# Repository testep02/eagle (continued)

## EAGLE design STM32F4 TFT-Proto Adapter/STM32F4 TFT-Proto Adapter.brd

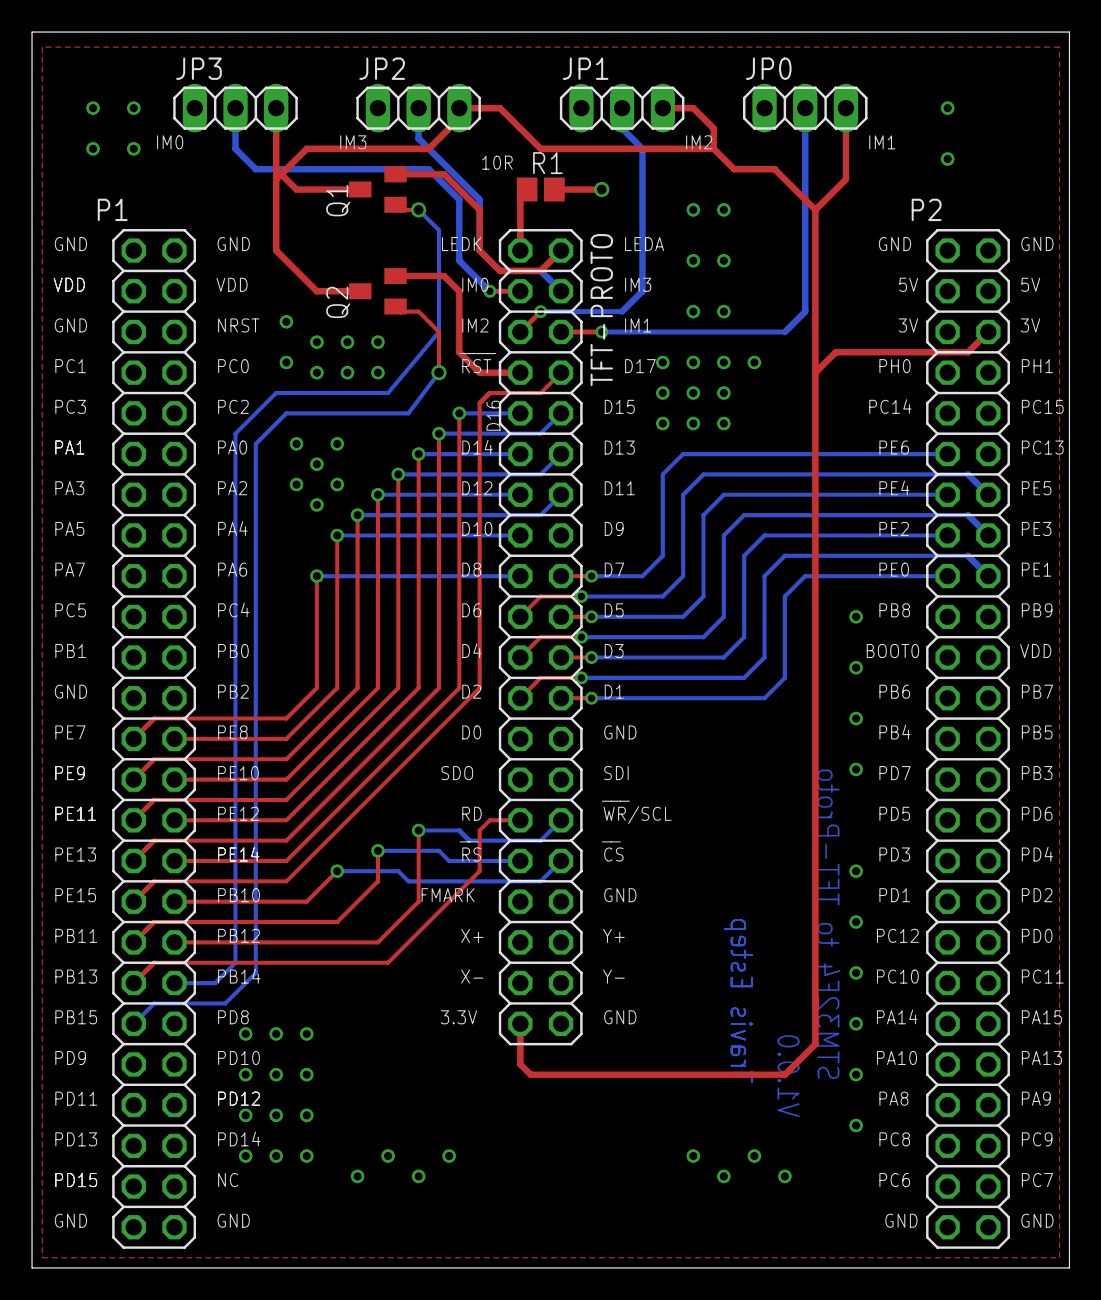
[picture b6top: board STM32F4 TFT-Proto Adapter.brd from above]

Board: 2 copper layers, 64.8 x 77.1 mm, 10 parts (0 on the bottom side), 31 nets.

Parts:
JP0, JP1, JP2, JP3: 1X03
P1, P2: 2X25
Q1, Q2: SOT23
R1: R0805
TFT-PROTO: 2X20

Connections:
CS: P1.34, TFT-PROTO.32
DAT1: P2.17, TFT-PROTO.24
DAT2: P2.18, TFT-PROTO.23
DAT3: P2.15, TFT-PROTO.22
DAT4: P2.16, TFT-PROTO.21
DAT5: P2.13, TFT-PROTO.20
DAT6: P2.14, TFT-PROTO.19
DAT7: P2.11, TFT-PROTO.18
DAT8: P1.25, TFT-PROTO.17
DAT10: P1.26, TFT-PROTO.15
DAT11: P1.27, TFT-PROTO.14
DAT12: P1.28, TFT-PROTO.13
DAT13: P1.29, TFT-PROTO.12
DAT14: P1.30, TFT-PROTO.11
DAT15: P1.31, TFT-PROTO.10
DAT16: P1.32, TFT-PROTO.9
DAT17: P1.33, TFT-PROTO.8
GND: JP0.1, JP1.1, JP2.1, JP3.1, P1.1, P1.2, P1.49, P1.50, P2.1, P2.2, P2.49, P2.50, R1.2, TFT-PROTO.16, TFT-PROTO.25, TFT-PROTO.26, TFT-PROTO.28, TFT-PROTO.34, TFT-PROTO.40
IM0: JP3.2, TFT-PROTO.3
IM1: JP0.2, TFT-PROTO.6
IM2: JP1.2, TFT-PROTO.5
IM3: JP2.2, TFT-PROTO.4
LEDA: P1.38, Q1.1
unnamed: R1.1, TFT-PROTO.1
unnamed: Q1.2, TFT-PROTO.2
unnamed: Q2.2, TFT-PROTO.7
PWR: JP0.3, JP1.3, JP2.3, JP3.3, P2.6, Q1.3, Q2.3, TFT-PROTO.39
RD: P1.37, TFT-PROTO.29
RS: P1.35, TFT-PROTO.31
RST: P1.39, Q2.1
WR: P1.36, TFT-PROTO.30

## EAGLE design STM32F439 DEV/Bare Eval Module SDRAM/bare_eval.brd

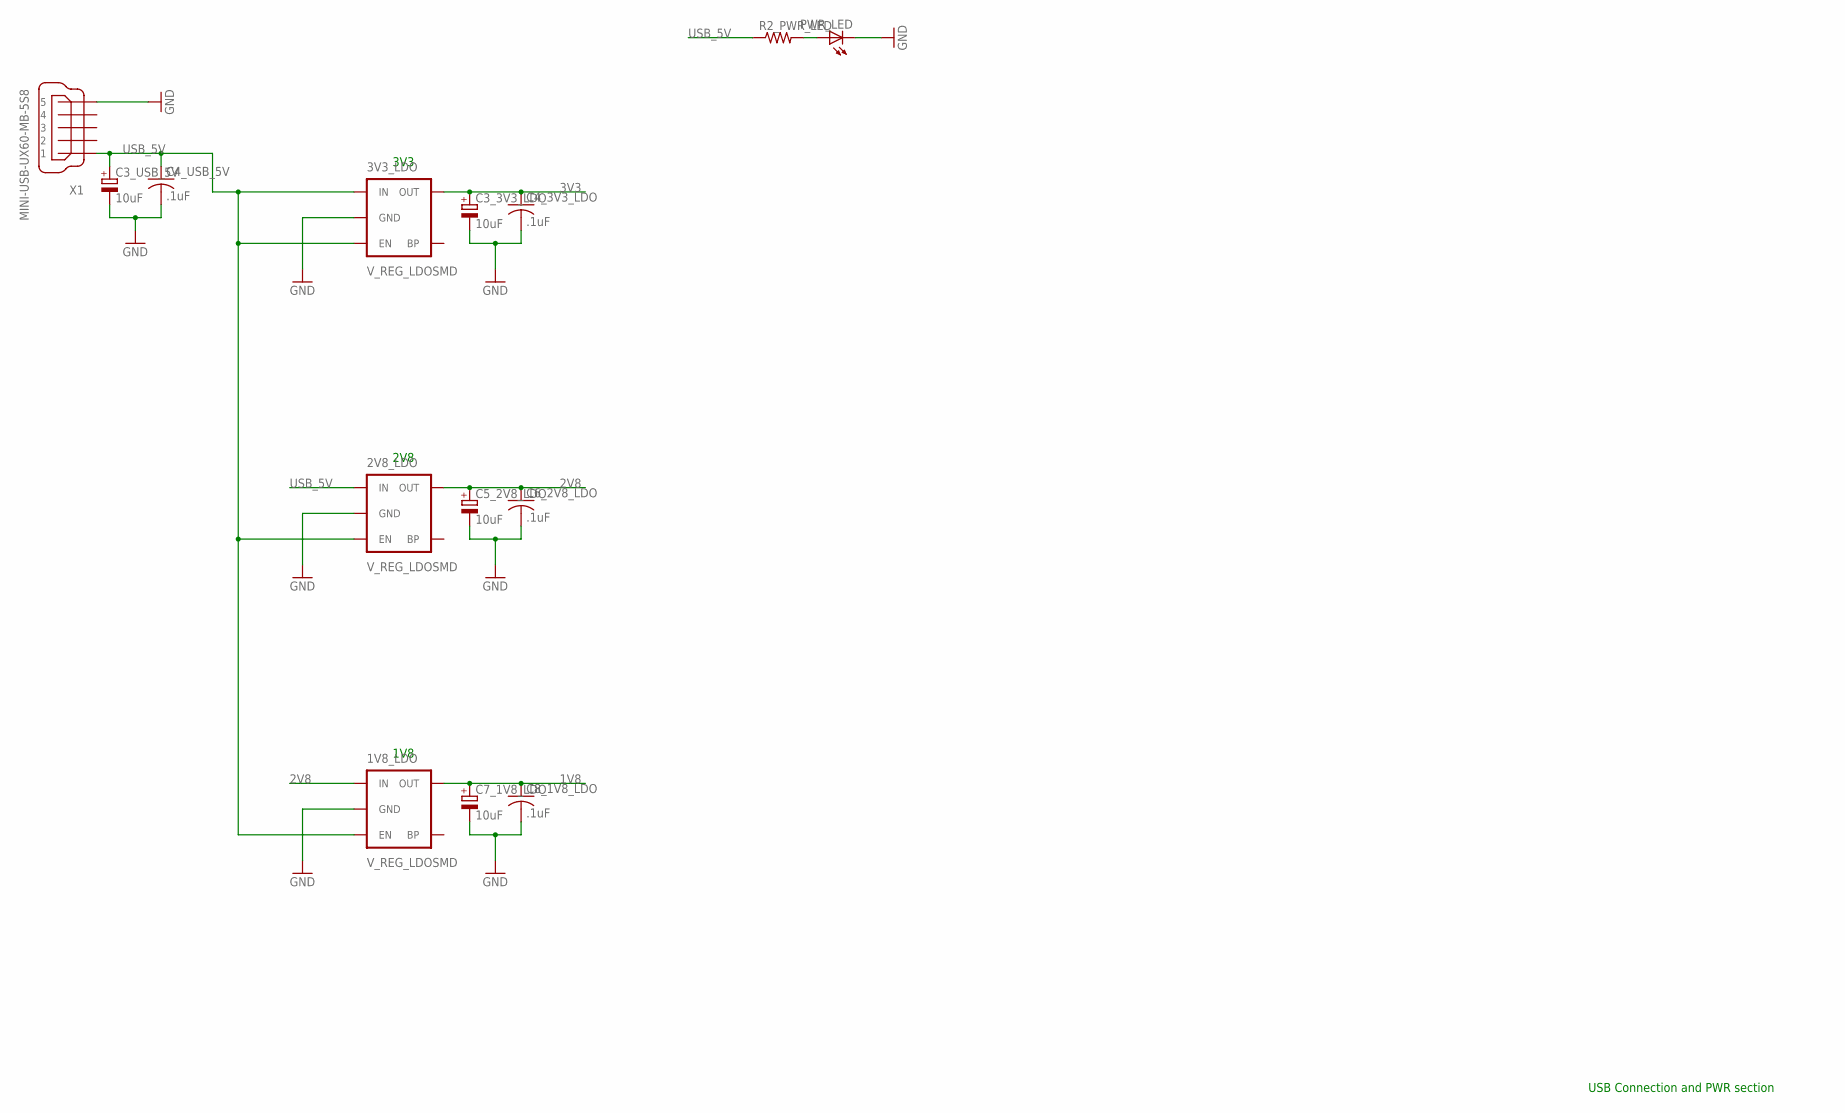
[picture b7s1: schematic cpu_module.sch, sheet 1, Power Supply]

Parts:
1V8_LDO, 2V8_LDO, 3V3_LDO: V_REG_LDOSMD; SOT23-5
C3_3V3_LDO, C3_USB_5V, C5_2V8_LDO, C7_1V8_LDO: 10uF; SMC_A
C4_3V3_LDO, C4_USB_5V, C6_2V8_LDO, C8_1V8_LDO: .1uF; C0402
PWR_LED: LEDCHIP-LED0603; CHIP-LED0603
R2_PWR_LED: RESISTOR0402-RES; 0402-RES
X1: MINI-USB-UX60-MB-5S8; UX60-MB-5S8

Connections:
3V3: 3V3_LDO.5 (OUT), C3_3V3_LDO.+, C4_3V3_LDO.1; also elsewhere on the board
GND: 1V8_LDO.2 (GND), 2V8_LDO.2 (GND), 3V3_LDO.2 (GND), C3_3V3_LDO.-, C3_USB_5V.-, C4_3V3_LDO.2, C4_USB_5V.2, C5_2V8_LDO.-, C6_2V8_LDO.2, C7_1V8_LDO.-, C8_1V8_LDO.2, PWR_LED.C, X1.5; also elsewhere on the board
unnamed: PWR_LED.A, R2_PWR_LED.2

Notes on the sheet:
USB Connection and PWR section
3V3
2V8
1V8

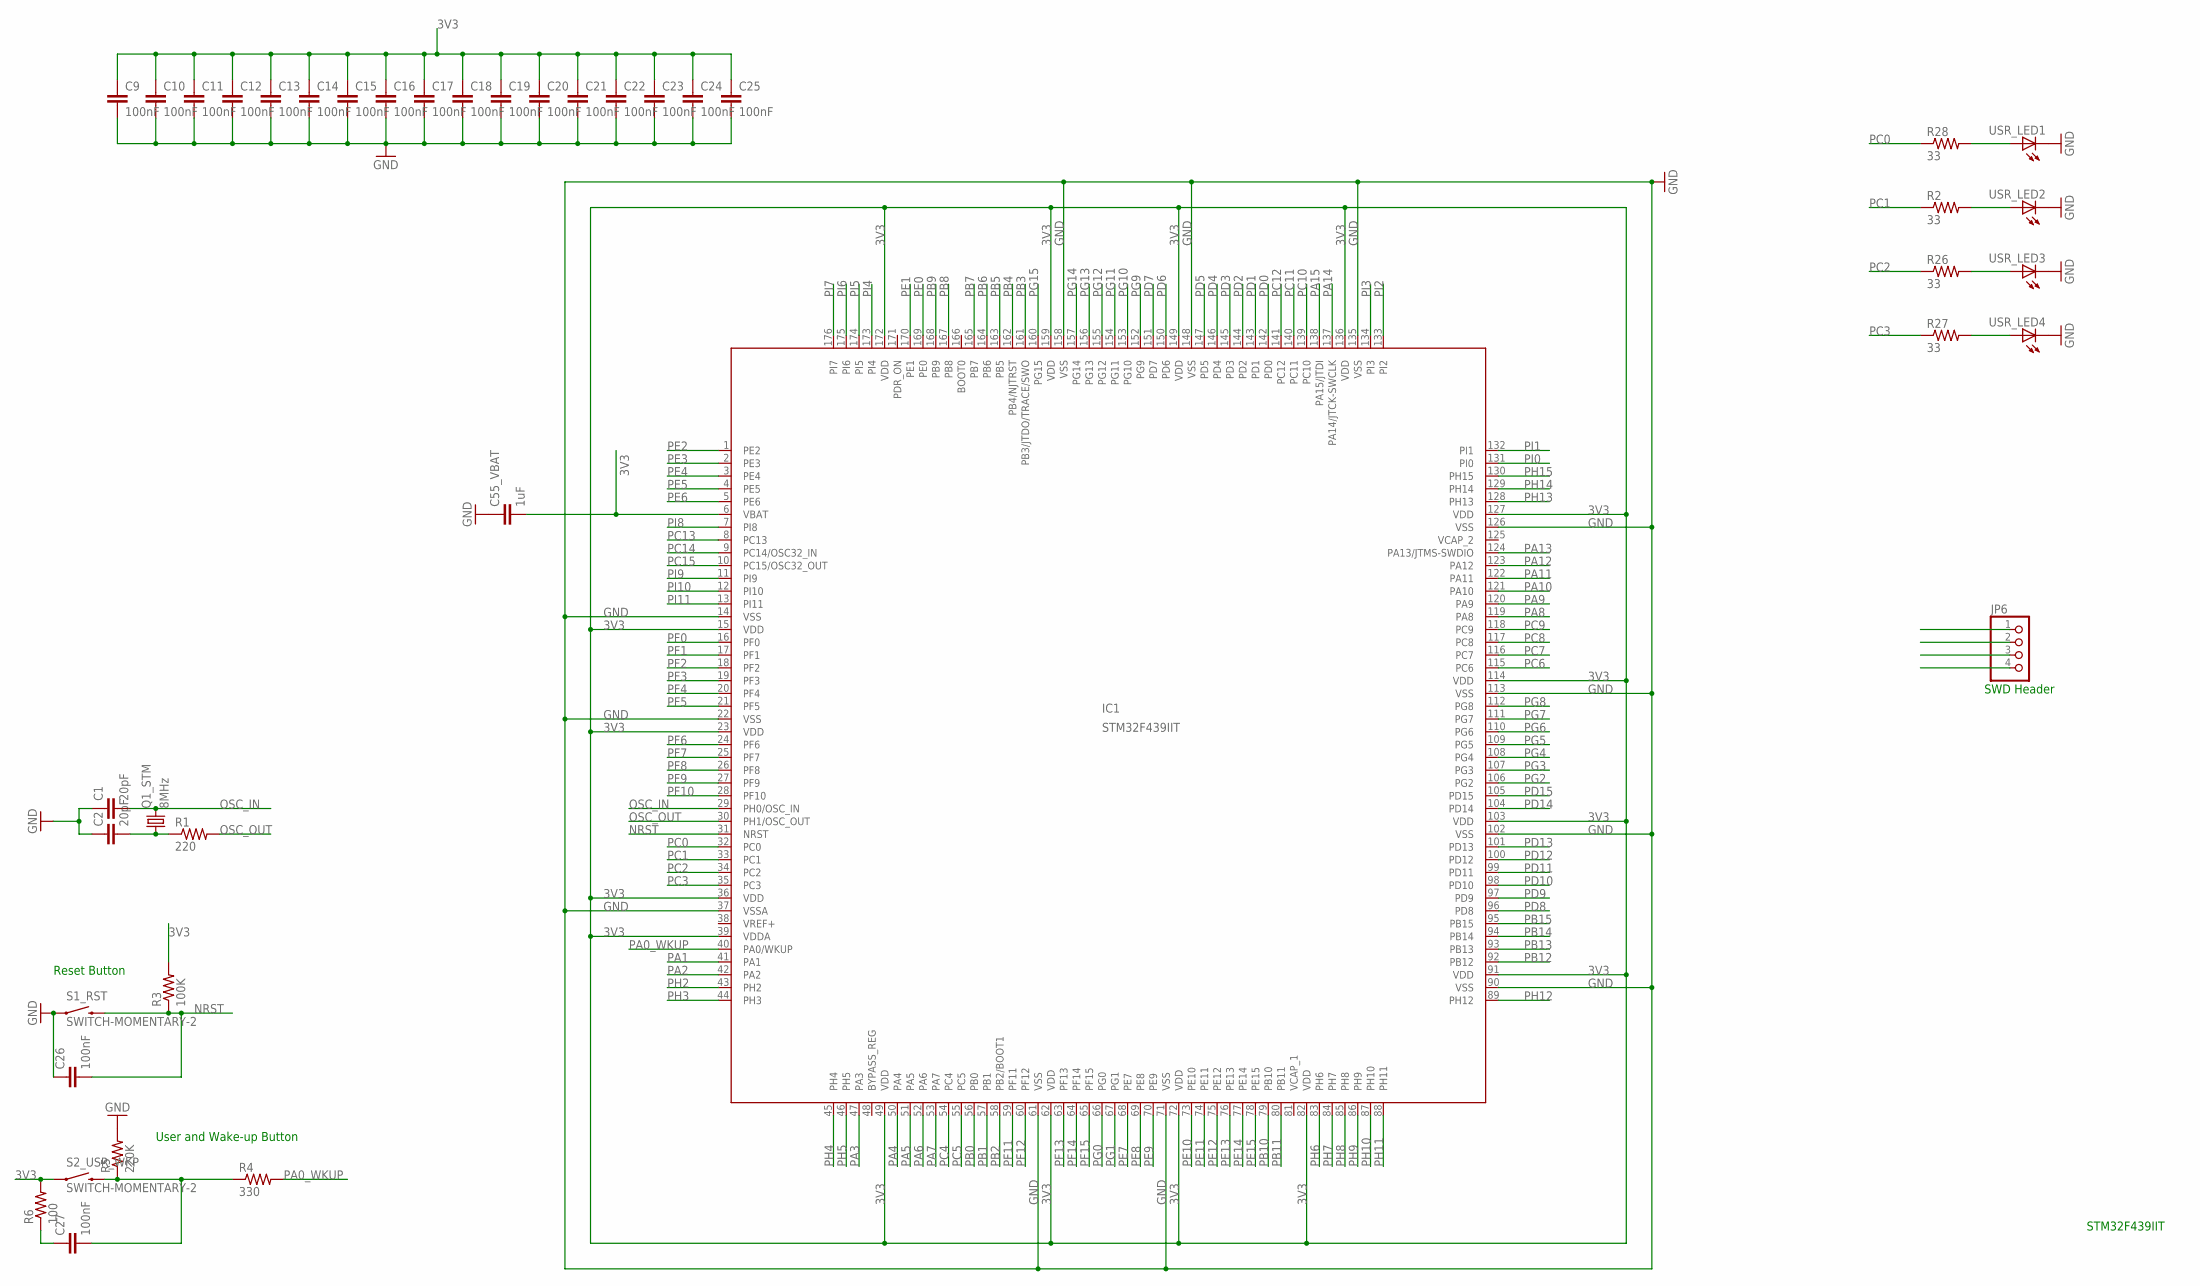
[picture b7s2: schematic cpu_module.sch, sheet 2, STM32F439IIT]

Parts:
C1, C2: 20pF; C0402
C9, C10, C11, C12, C13, C14, C15, C16, C17, C18, C19, C20, C21, C22, C23, C24, C25, C26, C27: 100nF; C0402
C55_VBAT: 1uF; C0402
IC1: STM32F439IIT; LQFP-176
JP6: PINHD-1X4/90; 1X04/90
Q1_STM: 8MHz; CTS406
R1: 220; 0402-RES
R2, R26, R27, R28: 33; 0402-RES
R3: 100K; 0402-RES
R4: 330; 0402-RES
R5: 220K; 0402-RES
R6: 100; 0402-RES
S1_RST, S2_USR_WKP: SWITCH-MOMENTARY-2; TACTILE_SWITCH_TALL
USR_LED1, USR_LED2, USR_LED3, USR_LED4: LEDCHIPLED_0805; CHIPLED_0805

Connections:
3V3: C9.1, C10.1, C11.1, C12.1, C13.1, C14.1, C15.1, C16.1, C17.1, C18.1, C19.1, C20.1, C21.1, C22.1, C23.1, C24.1, C25.1, C55_VBAT.2, IC1.6 (VBAT), IC1.15 (VDD), IC1.23 (VDD), IC1.36 (VDD), IC1.39 (VDDA), IC1.49 (VDD), IC1.62 (VDD), IC1.72 (VDD), IC1.82 (VDD), IC1.91 (VDD), IC1.103 (VDD), IC1.114 (VDD), IC1.127 (VDD), IC1.136 (VDD), IC1.149 (VDD), IC1.159 (VDD), IC1.172 (VDD), R3.2, R6.2, S2_USR_WKP.A2 (1); also elsewhere on the board
GND: C1.1, C2.1, C9.2, C10.2, C11.2, C12.2, C13.2, C14.2, C15.2, C16.2, C17.2, C18.2, C19.2, C20.2, C21.2, C22.2, C23.2, C24.2, C25.2, C26.1, C55_VBAT.1, IC1.14 (VSS), IC1.22 (VSS), IC1.37 (VSSA), IC1.61 (VSS), IC1.71 (VSS), IC1.90 (VSS), IC1.102 (VSS), IC1.113 (VSS), IC1.126 (VSS), IC1.135 (VSS), IC1.148 (VSS), IC1.158 (VSS), R5.2, S1_RST.A2 (1), USR_LED1.C, USR_LED2.C, USR_LED3.C, USR_LED4.C; also elsewhere on the board
unnamed: C2.2, Q1_STM.1, R1.1
unnamed: C27.2, R4.1, R5.1, S2_USR_WKP.B2 (2)
unnamed: C27.1, R6.1
unnamed: R28.2, USR_LED1.A
unnamed: R2.2, USR_LED2.A
unnamed: R26.2, USR_LED3.A
unnamed: R27.2, USR_LED4.A
NRST: C26.2, IC1.31 (NRST), R3.1, S1_RST.B2 (2); also elsewhere on the board
OSC_IN: C1.2, IC1.29 (PH0/OSC_IN), Q1_STM.3 (2)
OSC_OUT: IC1.30 (PH1/OSC_OUT), R1.2
PA0_WKUP: IC1.40 (PA0/WKUP), R4.2
PA1: IC1.41 (PA1); also elsewhere on the board
PA2: IC1.42 (PA2); also elsewhere on the board
PA3: IC1.47 (PA3); also elsewhere on the board
PA4: IC1.50 (PA4); also elsewhere on the board
PA5: IC1.51 (PA5); also elsewhere on the board
PA6: IC1.52 (PA6); also elsewhere on the board
PA7: IC1.53 (PA7); also elsewhere on the board
PA8: IC1.119 (PA8); also elsewhere on the board
PA9: IC1.120 (PA9); also elsewhere on the board
PA10: IC1.121 (PA10); also elsewhere on the board
PA11: IC1.122 (PA11); also elsewhere on the board
PA12: IC1.123 (PA12); also elsewhere on the board
PA13: IC1.124 (PA13/JTMS-SWDIO)
PA14: IC1.137 (PA14/JTCK-SWCLK); also elsewhere on the board
PA15: IC1.138 (PA15/JTDI); also elsewhere on the board
PB0: IC1.56 (PB0); also elsewhere on the board
PB1: IC1.57 (PB1); also elsewhere on the board
PB2: IC1.58 (PB2/BOOT1); also elsewhere on the board
PB3: IC1.161 (PB3/JTDO/TRACE/SWO); also elsewhere on the board
PB4: IC1.162 (PB4/NJTRST); also elsewhere on the board
PB5: IC1.163 (PB5); also elsewhere on the board
PB6: IC1.164 (PB6); also elsewhere on the board
PB7: IC1.165 (PB7); also elsewhere on the board
PB8: IC1.167 (PB8); also elsewhere on the board
PB9: IC1.168 (PB9); also elsewhere on the board
PB10: IC1.79 (PB10); also elsewhere on the board
PB11: IC1.80 (PB11); also elsewhere on the board
PB12: IC1.92 (PB12); also elsewhere on the board
PB13: IC1.93 (PB13); also elsewhere on the board
PB14: IC1.94 (PB14); also elsewhere on the board
PB15: IC1.95 (PB15); also elsewhere on the board
PC0: IC1.32 (PC0), R28.1; also elsewhere on the board
PC1: IC1.33 (PC1), R2.1; also elsewhere on the board
PC2: IC1.34 (PC2), R26.1; also elsewhere on the board
PC3: IC1.35 (PC3), R27.1; also elsewhere on the board
PC4: IC1.54 (PC4); also elsewhere on the board
PC5: IC1.55 (PC5); also elsewhere on the board
PC6: IC1.115 (PC6); also elsewhere on the board
PC7: IC1.116 (PC7); also elsewhere on the board
PC8: IC1.117 (PC8); also elsewhere on the board
PC9: IC1.118 (PC9); also elsewhere on the board
PC10: IC1.139 (PC10); also elsewhere on the board
PC11: IC1.140 (PC11); also elsewhere on the board
PC12: IC1.141 (PC12); also elsewhere on the board
PC13: IC1.8 (PC13); also elsewhere on the board
PC14: IC1.9 (PC14/OSC32_IN); also elsewhere on the board
PC15: IC1.10 (PC15/OSC32_OUT); also elsewhere on the board
PD0: IC1.142 (PD0); also elsewhere on the board
PD1: IC1.143 (PD1); also elsewhere on the board
PD2: IC1.144 (PD2); also elsewhere on the board
PD3: IC1.145 (PD3); also elsewhere on the board
PD4: IC1.146 (PD4); also elsewhere on the board
PD5: IC1.147 (PD5); also elsewhere on the board
PD6: IC1.150 (PD6); also elsewhere on the board
PD7: IC1.151 (PD7); also elsewhere on the board
PD8: IC1.96 (PD8); also elsewhere on the board
PD9: IC1.97 (PD9); also elsewhere on the board
PD10: IC1.98 (PD10); also elsewhere on the board
PD11: IC1.99 (PD11); also elsewhere on the board
PD12: IC1.100 (PD12); also elsewhere on the board
PD13: IC1.101 (PD13); also elsewhere on the board
PD14: IC1.104 (PD14); also elsewhere on the board
PD15: IC1.105 (PD15); also elsewhere on the board
PDR_ON: IC1.171 (PDR_ON)
PE0: IC1.169 (PE0); also elsewhere on the board
PE1: IC1.170 (PE1); also elsewhere on the board
PE2: IC1.1 (PE2); also elsewhere on the board
PE3: IC1.2 (PE3); also elsewhere on the board
PE4: IC1.3 (PE4); also elsewhere on the board
PE5: IC1.4 (PE5); also elsewhere on the board
PE6: IC1.5 (PE6); also elsewhere on the board
PE7: IC1.68 (PE7); also elsewhere on the board
PE8: IC1.69 (PE8); also elsewhere on the board
PE9: IC1.70 (PE9); also elsewhere on the board
PE10: IC1.73 (PE10); also elsewhere on the board
PE11: IC1.74 (PE11); also elsewhere on the board
PE12: IC1.75 (PE12); also elsewhere on the board
PE13: IC1.76 (PE13); also elsewhere on the board
PE14: IC1.77 (PE14); also elsewhere on the board
PE15: IC1.78 (PE15); also elsewhere on the board
PF0: IC1.16 (PF0); also elsewhere on the board
PF1: IC1.17 (PF1); also elsewhere on the board
PF2: IC1.18 (PF2); also elsewhere on the board
PF3: IC1.19 (PF3); also elsewhere on the board
PF4: IC1.20 (PF4); also elsewhere on the board
PF5: IC1.21 (PF5); also elsewhere on the board
PF6: IC1.24 (PF6); also elsewhere on the board
PF7: IC1.25 (PF7); also elsewhere on the board
PF8: IC1.26 (PF8); also elsewhere on the board
PF9: IC1.27 (PF9); also elsewhere on the board
PF10: IC1.28 (PF10); also elsewhere on the board
PF11: IC1.59 (PF11); also elsewhere on the board
PF12: IC1.60 (PF12); also elsewhere on the board
PF13: IC1.63 (PF13); also elsewhere on the board
PF14: IC1.64 (PF14); also elsewhere on the board
PF15: IC1.65 (PF15); also elsewhere on the board
PG0: IC1.66 (PG0); also elsewhere on the board
PG1: IC1.67 (PG1); also elsewhere on the board
PG2: IC1.106 (PG2); also elsewhere on the board
PG3: IC1.107 (PG3); also elsewhere on the board
PG4: IC1.108 (PG4); also elsewhere on the board
PG5: IC1.109 (PG5); also elsewhere on the board
PG6: IC1.110 (PG6); also elsewhere on the board
PG7: IC1.111 (PG7); also elsewhere on the board
PG8: IC1.112 (PG8); also elsewhere on the board
PG9: IC1.152 (PG9); also elsewhere on the board
PG10: IC1.153 (PG10); also elsewhere on the board
PG11: IC1.154 (PG11); also elsewhere on the board
PG12: IC1.155 (PG12); also elsewhere on the board
PG13: IC1.156 (PG13); also elsewhere on the board
PG14: IC1.157 (PG14); also elsewhere on the board
PG15: IC1.160 (PG15); also elsewhere on the board
PH2: IC1.43 (PH2); also elsewhere on the board
PH3: IC1.44 (PH3); also elsewhere on the board
PH4: IC1.45 (PH4); also elsewhere on the board
PH5: IC1.46 (PH5); also elsewhere on the board
PH6: IC1.83 (PH6); also elsewhere on the board
PH7: IC1.84 (PH7); also elsewhere on the board
PH8: IC1.85 (PH8); also elsewhere on the board
PH9: IC1.86 (PH9); also elsewhere on the board
PH10: IC1.87 (PH10); also elsewhere on the board
PH11: IC1.88 (PH11); also elsewhere on the board
PH12: IC1.89 (PH12); also elsewhere on the board
PI2: IC1.133 (PI2); also elsewhere on the board
PI3: IC1.134 (PI3); also elsewhere on the board
PI4: IC1.173 (PI4); also elsewhere on the board
PI5: IC1.174 (PI5); also elsewhere on the board
PI6: IC1.175 (PI6); also elsewhere on the board
PI7: IC1.176 (PI7); also elsewhere on the board
PI8: IC1.7 (PI8); also elsewhere on the board
PI9: IC1.11 (PI9); also elsewhere on the board
PI10: IC1.12 (PI10); also elsewhere on the board
PI11: IC1.13 (PI11); also elsewhere on the board
VCAP_1: IC1.81 (VCAP_1)
VCAP_2: IC1.125 (VCAP_2)
VREF+: IC1.38 (VREF+)

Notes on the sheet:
STM32F439IIT
Reset Button
User and Wake-up Button
SWD Header

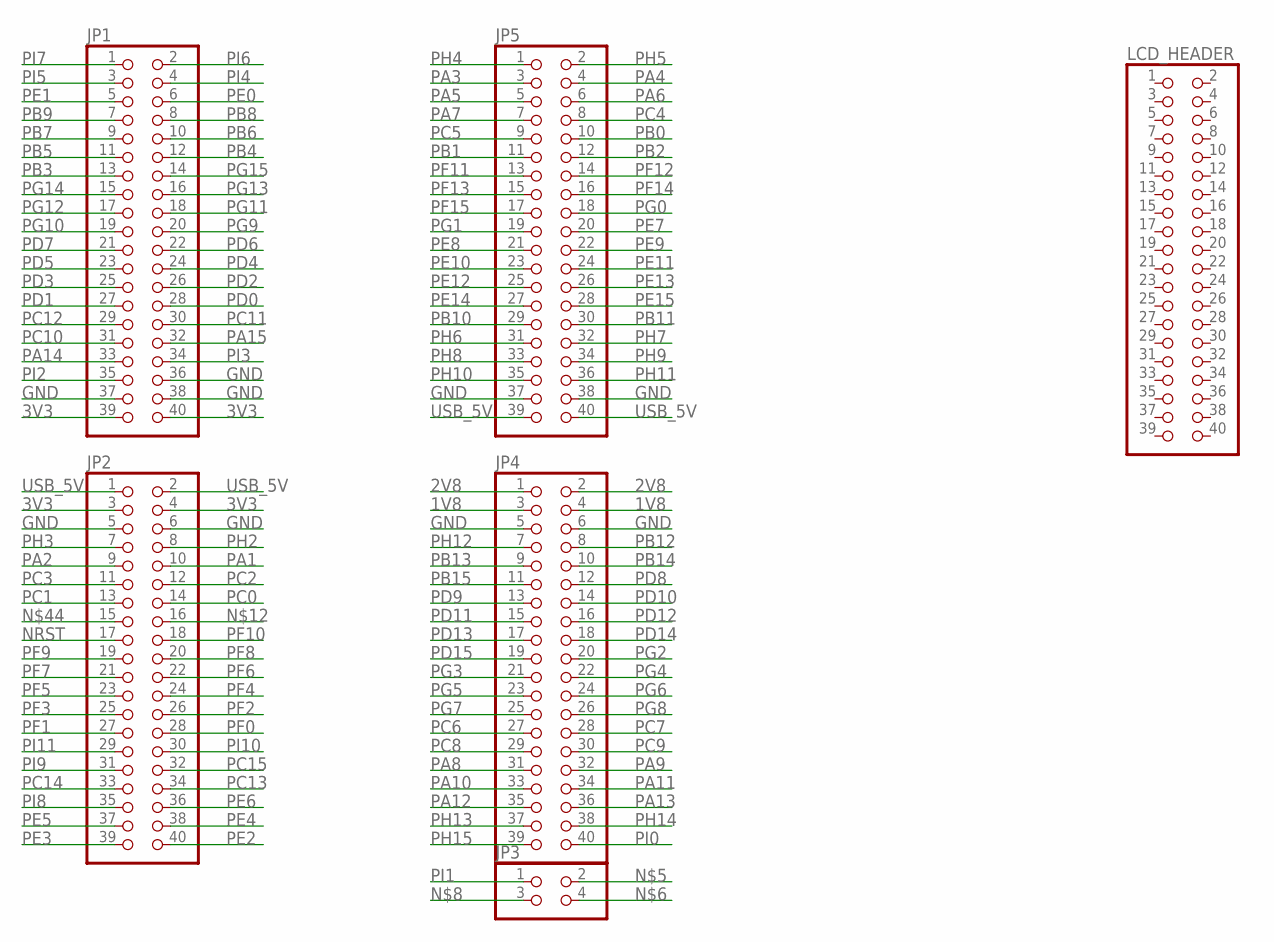
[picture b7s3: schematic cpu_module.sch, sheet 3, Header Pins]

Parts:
JP1, JP2, JP4, JP5: PINHD-2X20; 2X20
JP3: PINHD-2X2; 2X02
LCD_HEADER: PINHD-2X20; 2X20

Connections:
3V3: JP1.39, JP1.40, JP2.3, JP2.4; also elsewhere on the board
GND: JP1.36, JP1.37, JP1.38, JP2.5, JP2.6, JP4.5, JP4.6, JP5.37, JP5.38; also elsewhere on the board
NRST: JP2.17; also elsewhere on the board
PA1: JP2.10; also elsewhere on the board
PA2: JP2.9; also elsewhere on the board
PA3: JP5.3; also elsewhere on the board
PA4: JP5.4; also elsewhere on the board
PA5: JP5.5; also elsewhere on the board
PA6: JP5.6; also elsewhere on the board
PA7: JP5.7; also elsewhere on the board
PA8: JP4.31; also elsewhere on the board
PA9: JP4.32; also elsewhere on the board
PA10: JP4.33; also elsewhere on the board
PA11: JP4.34; also elsewhere on the board
PA12: JP4.35; also elsewhere on the board
PA14: JP1.33; also elsewhere on the board
PA15: JP1.32; also elsewhere on the board
PB0: JP5.10; also elsewhere on the board
PB1: JP5.11; also elsewhere on the board
PB2: JP5.12; also elsewhere on the board
PB3: JP1.13; also elsewhere on the board
PB4: JP1.12; also elsewhere on the board
PB5: JP1.11; also elsewhere on the board
PB6: JP1.10; also elsewhere on the board
PB7: JP1.9; also elsewhere on the board
PB8: JP1.8; also elsewhere on the board
PB9: JP1.7; also elsewhere on the board
PB10: JP5.29; also elsewhere on the board
PB11: JP5.30; also elsewhere on the board
PB12: JP4.8; also elsewhere on the board
PB13: JP4.9; also elsewhere on the board
PB14: JP4.10; also elsewhere on the board
PB15: JP4.11; also elsewhere on the board
PC0: JP2.14; also elsewhere on the board
PC1: JP2.13; also elsewhere on the board
PC2: JP2.12; also elsewhere on the board
PC3: JP2.11; also elsewhere on the board
PC4: JP5.8; also elsewhere on the board
PC5: JP5.9; also elsewhere on the board
PC6: JP4.27; also elsewhere on the board
PC7: JP4.28; also elsewhere on the board
PC8: JP4.29; also elsewhere on the board
PC9: JP4.30; also elsewhere on the board
PC10: JP1.31; also elsewhere on the board
PC11: JP1.30; also elsewhere on the board
PC12: JP1.29; also elsewhere on the board
PC13: JP2.34; also elsewhere on the board
PC14: JP2.33; also elsewhere on the board
PC15: JP2.32; also elsewhere on the board
PD0: JP1.28; also elsewhere on the board
PD1: JP1.27; also elsewhere on the board
PD2: JP1.26; also elsewhere on the board
PD3: JP1.25; also elsewhere on the board
PD4: JP1.24; also elsewhere on the board
PD5: JP1.23; also elsewhere on the board
PD6: JP1.22; also elsewhere on the board
PD7: JP1.21; also elsewhere on the board
PD8: JP4.12; also elsewhere on the board
PD9: JP4.13; also elsewhere on the board
PD10: JP4.14; also elsewhere on the board
PD11: JP4.15; also elsewhere on the board
PD12: JP4.16; also elsewhere on the board
PD13: JP4.17; also elsewhere on the board
PD14: JP4.18; also elsewhere on the board
PD15: JP4.19; also elsewhere on the board
PE0: JP1.6; also elsewhere on the board
PE1: JP1.5; also elsewhere on the board
PE2: JP2.40; also elsewhere on the board
PE3: JP2.39; also elsewhere on the board
PE4: JP2.38; also elsewhere on the board
PE5: JP2.37; also elsewhere on the board
PE6: JP2.36; also elsewhere on the board
PE7: JP5.20; also elsewhere on the board
PE8: JP5.21; also elsewhere on the board
PE9: JP5.22; also elsewhere on the board
PE10: JP5.23; also elsewhere on the board
PE11: JP5.24; also elsewhere on the board
PE12: JP5.25; also elsewhere on the board
PE13: JP5.26; also elsewhere on the board
PE14: JP5.27; also elsewhere on the board
PE15: JP5.28; also elsewhere on the board
PF0: JP2.28; also elsewhere on the board
PF1: JP2.27; also elsewhere on the board
PF2: JP2.26; also elsewhere on the board
PF3: JP2.25; also elsewhere on the board
PF4: JP2.24; also elsewhere on the board
PF5: JP2.23; also elsewhere on the board
PF6: JP2.22; also elsewhere on the board
PF7: JP2.21; also elsewhere on the board
PF8: JP2.20; also elsewhere on the board
PF9: JP2.19; also elsewhere on the board
PF10: JP2.18; also elsewhere on the board
PF11: JP5.13; also elsewhere on the board
PF12: JP5.14; also elsewhere on the board
PF13: JP5.15; also elsewhere on the board
PF14: JP5.16; also elsewhere on the board
PF15: JP5.17; also elsewhere on the board
PG0: JP5.18; also elsewhere on the board
PG1: JP5.19; also elsewhere on the board
PG2: JP4.20; also elsewhere on the board
PG3: JP4.21; also elsewhere on the board
PG4: JP4.22; also elsewhere on the board
PG5: JP4.23; also elsewhere on the board
PG6: JP4.24; also elsewhere on the board
PG7: JP4.25; also elsewhere on the board
PG8: JP4.26; also elsewhere on the board
PG9: JP1.20; also elsewhere on the board
PG10: JP1.19; also elsewhere on the board
PG11: JP1.18; also elsewhere on the board
PG12: JP1.17; also elsewhere on the board
PG13: JP1.16; also elsewhere on the board
PG14: JP1.15; also elsewhere on the board
PG15: JP1.14; also elsewhere on the board
PH2: JP2.8; also elsewhere on the board
PH3: JP2.7; also elsewhere on the board
PH4: JP5.1; also elsewhere on the board
PH5: JP5.2; also elsewhere on the board
PH6: JP5.31; also elsewhere on the board
PH7: JP5.32; also elsewhere on the board
PH8: JP5.33; also elsewhere on the board
PH9: JP5.34; also elsewhere on the board
PH10: JP5.35; also elsewhere on the board
PH11: JP5.36; also elsewhere on the board
PH12: JP4.7; also elsewhere on the board
PI2: JP1.35; also elsewhere on the board
PI3: JP1.34; also elsewhere on the board
PI4: JP1.4; also elsewhere on the board
PI5: JP1.3; also elsewhere on the board
PI6: JP1.2; also elsewhere on the board
PI7: JP1.1; also elsewhere on the board
PI8: JP2.35; also elsewhere on the board
PI9: JP2.31; also elsewhere on the board
PI10: JP2.30; also elsewhere on the board
PI11: JP2.29; also elsewhere on the board

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
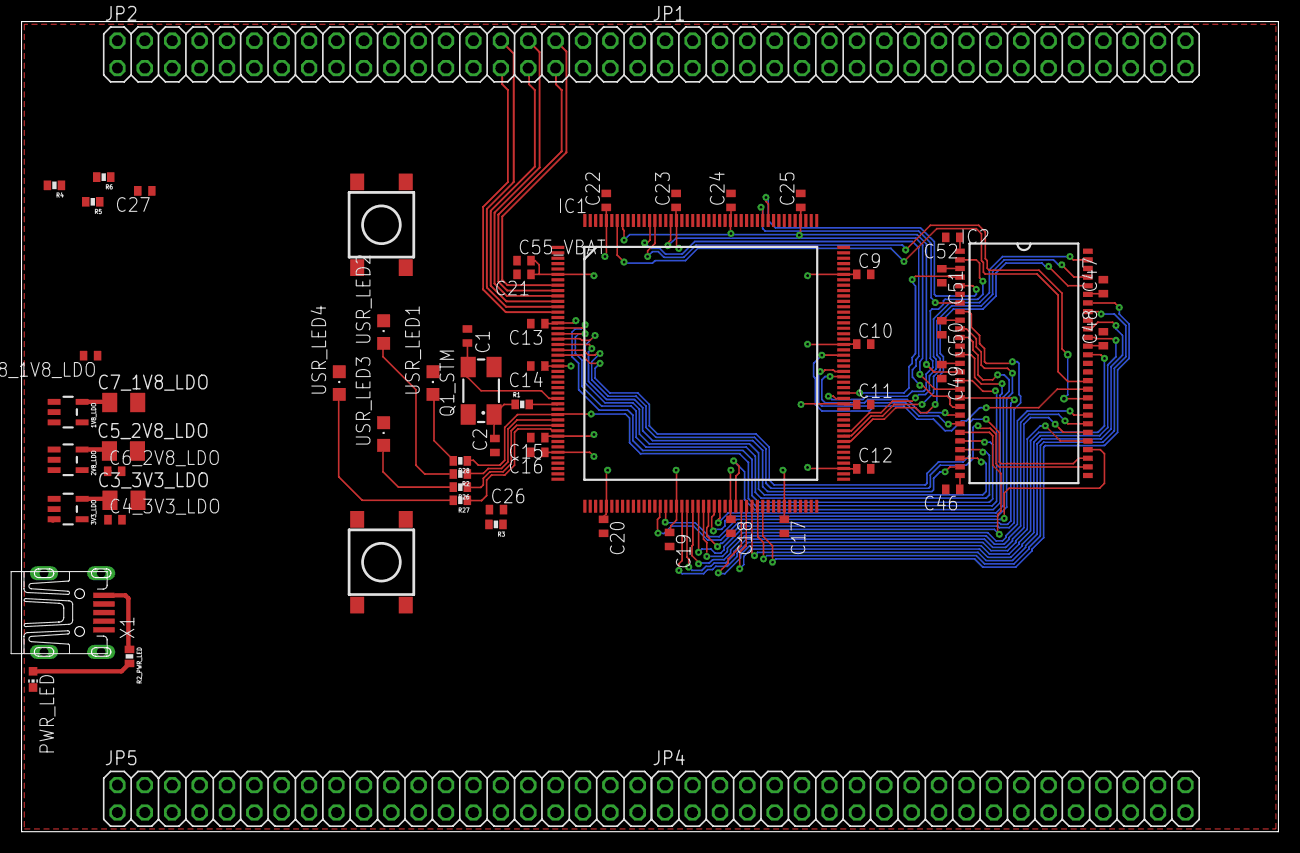
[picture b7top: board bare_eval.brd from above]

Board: 4 copper layers, 116.6 x 75.1 mm, 63 parts (0 on the bottom side), 153 nets.

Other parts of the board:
C46, C47, C48, C49, C50, C51, C52: 100nF; C0402
IC2: IS42S16400J; TSOP-2

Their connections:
3V3: C46.1, C47.1, C48.1, C49.1, C50.1, C51.1, C52.1, IC2.1, IC2.3, IC2.9, IC2.14, IC2.27, IC2.43, IC2.49; also elsewhere on the board
GND: C46.2, C47.2, C48.2, C49.2, C50.2, C51.2, C52.2, IC2.6, IC2.12, IC2.28, IC2.41, IC2.46, IC2.52, IC2.54; also elsewhere on the board
PB5: IC2.37; also elsewhere on the board
PB6: IC2.19; also elsewhere on the board
PC0: IC2.16; also elsewhere on the board
PD0: IC2.5; also elsewhere on the board
PD1: IC2.7; also elsewhere on the board
PD8: IC2.50; also elsewhere on the board
PD9: IC2.51; also elsewhere on the board
PD10: IC2.53; also elsewhere on the board
PD14: IC2.2; also elsewhere on the board
PD15: IC2.4; also elsewhere on the board
PE0: IC2.15; also elsewhere on the board
PE1: IC2.39; also elsewhere on the board
PE7: IC2.8; also elsewhere on the board
PE8: IC2.10; also elsewhere on the board
PE9: IC2.11; also elsewhere on the board
PE10: IC2.13; also elsewhere on the board
PE11: IC2.42; also elsewhere on the board
PE12: IC2.44; also elsewhere on the board
PE13: IC2.45; also elsewhere on the board
PE14: IC2.47; also elsewhere on the board
PE15: IC2.48; also elsewhere on the board
PF0: IC2.23; also elsewhere on the board
PF1: IC2.24; also elsewhere on the board
PF2: IC2.25; also elsewhere on the board
PF3: IC2.26; also elsewhere on the board
PF4: IC2.29; also elsewhere on the board
PF5: IC2.30; also elsewhere on the board
PF11: IC2.18; also elsewhere on the board
PF12: IC2.31; also elsewhere on the board
PF13: IC2.32; also elsewhere on the board
PF14: IC2.33; also elsewhere on the board
PF15: IC2.34; also elsewhere on the board
PG0: IC2.22; also elsewhere on the board
PG1: IC2.35; also elsewhere on the board
PG4: IC2.20; also elsewhere on the board
PG5: IC2.21; also elsewhere on the board
PG8: IC2.38; also elsewhere on the board
PG15: IC2.17; also elsewhere on the board
